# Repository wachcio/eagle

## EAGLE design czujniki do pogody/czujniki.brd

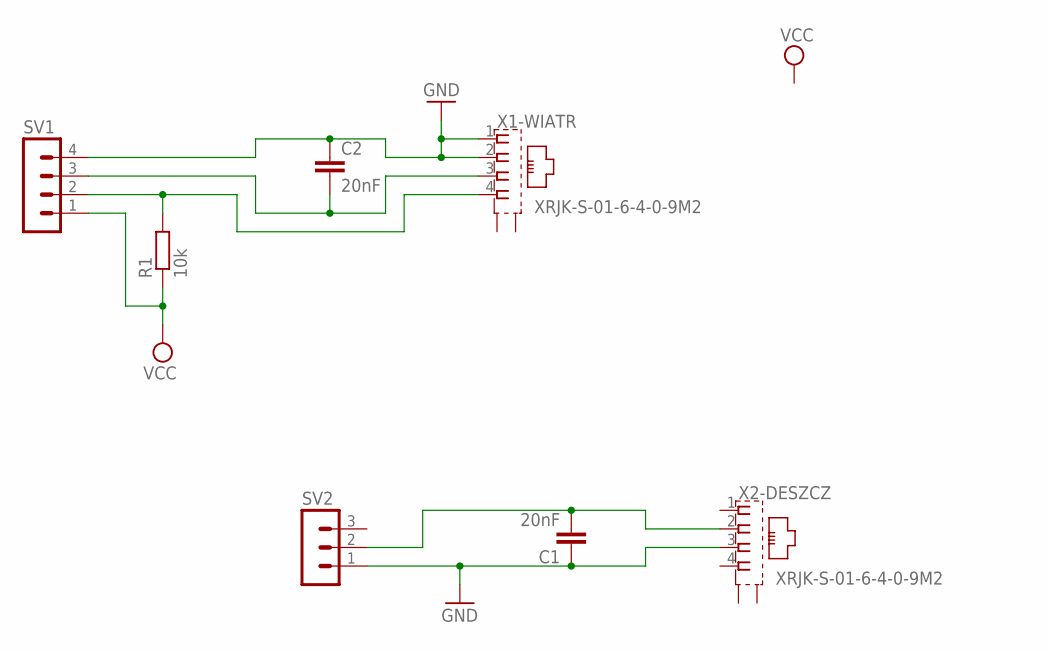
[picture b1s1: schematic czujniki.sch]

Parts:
C1, C2: 20nF; C2.5-2
R1: 10k; M1206
SV1: MA04-1
SV2: MA03-1
X1-WIATR, X2-DESZCZ: XRJK-S-01-6-4-0-9M2

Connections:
GND: C1.1, C2.1, SV1.4, SV2.1, X1-WIATR.1, X1-WIATR.2, X2-DESZCZ.3
unnamed: C1.2, SV2.2, X2-DESZCZ.2
unnamed: C2.2, SV1.3, X1-WIATR.3
unnamed: R1.2, SV1.2, X1-WIATR.4
VCC: R1.1, SV1.1

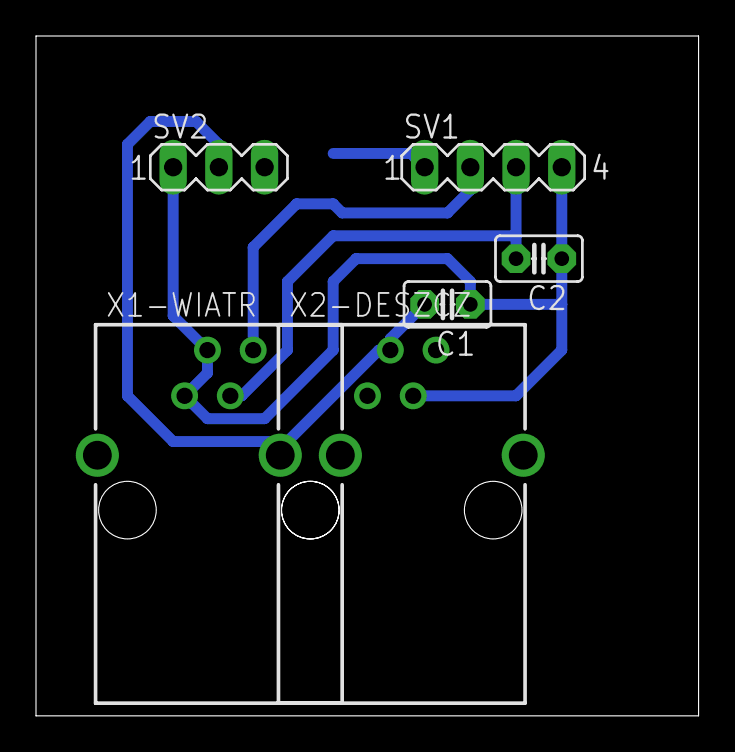
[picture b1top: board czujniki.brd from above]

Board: 2 copper layers, 36.8 x 37.8 mm, 7 parts (1 on the bottom side), 5 nets.

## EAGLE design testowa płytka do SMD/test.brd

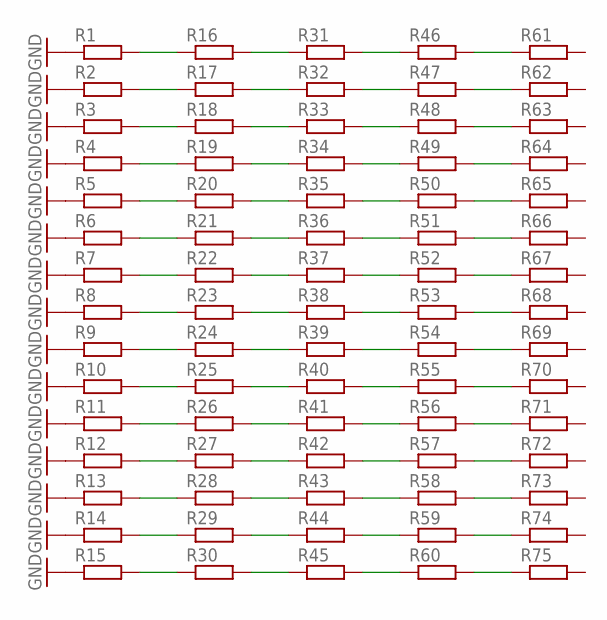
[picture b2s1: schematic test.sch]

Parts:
R1, R2, R3, R4, R5, R6, R7, R8, R9, R10, R11, R12, R13, R14, R15, R16, R17, R18, R19, R20, R21, R22, R23, R24, R25, R26, R27, R28, R29, R30, R31, R32, R33, R34, R35, R36, R37, R38, R39, R40, R41, R42, R43, R44, R45, R46, R47, R48, R49, R50, R51, R52, R53, R54, R55, R56, R57, R58, R59, R60, R61, R62, R63, R64, R65, R66, R67, R68, R69, R70, R71, R72, R73, R74, R75: R-EU_R1206; R1206

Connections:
GND: R1.1, R2.1, R3.1, R4.1, R5.1, R6.1, R7.1, R8.1, R9.1, R10.1, R11.1, R12.1, R13.1, R14.1, R15.1
unnamed: R46.2, R61.1
unnamed: R1.2, R16.1
unnamed: R2.2, R17.1
unnamed: R3.2, R18.1
unnamed: R4.2, R19.1
unnamed: R5.2, R20.1
unnamed: R6.2, R21.1
unnamed: R7.2, R22.1
unnamed: R8.2, R23.1
unnamed: R9.2, R24.1
unnamed: R10.2, R25.1
unnamed: R11.2, R26.1
unnamed: R12.2, R27.1
unnamed: R13.2, R28.1
unnamed: R14.2, R29.1
unnamed: R15.2, R30.1
unnamed: R16.2, R31.1
unnamed: R17.2, R32.1
unnamed: R18.2, R33.1
unnamed: R19.2, R34.1
unnamed: R20.2, R35.1
unnamed: R21.2, R36.1
unnamed: R22.2, R37.1
unnamed: R23.2, R38.1
unnamed: R24.2, R39.1
unnamed: R25.2, R40.1
unnamed: R26.2, R41.1
unnamed: R27.2, R42.1
unnamed: R28.2, R43.1
unnamed: R29.2, R44.1
unnamed: R30.2, R45.1
unnamed: R31.2, R46.1
unnamed: R32.2, R47.1
unnamed: R33.2, R48.1
unnamed: R34.2, R49.1
unnamed: R35.2, R50.1
unnamed: R36.2, R51.1
unnamed: R37.2, R52.1
unnamed: R38.2, R53.1
unnamed: R39.2, R54.1
unnamed: R40.2, R55.1
unnamed: R41.2, R56.1
unnamed: R42.2, R57.1
unnamed: R43.2, R58.1
unnamed: R44.2, R59.1
unnamed: R45.2, R60.1
unnamed: R47.2, R62.1
unnamed: R48.2, R63.1
unnamed: R49.2, R64.1
unnamed: R50.2, R65.1
unnamed: R51.2, R66.1
unnamed: R52.2, R67.1
unnamed: R53.2, R68.1
unnamed: R54.2, R69.1
unnamed: R55.2, R70.1
unnamed: R56.2, R71.1
unnamed: R57.2, R72.1
unnamed: R58.2, R73.1
unnamed: R59.2, R74.1
unnamed: R60.2, R75.1

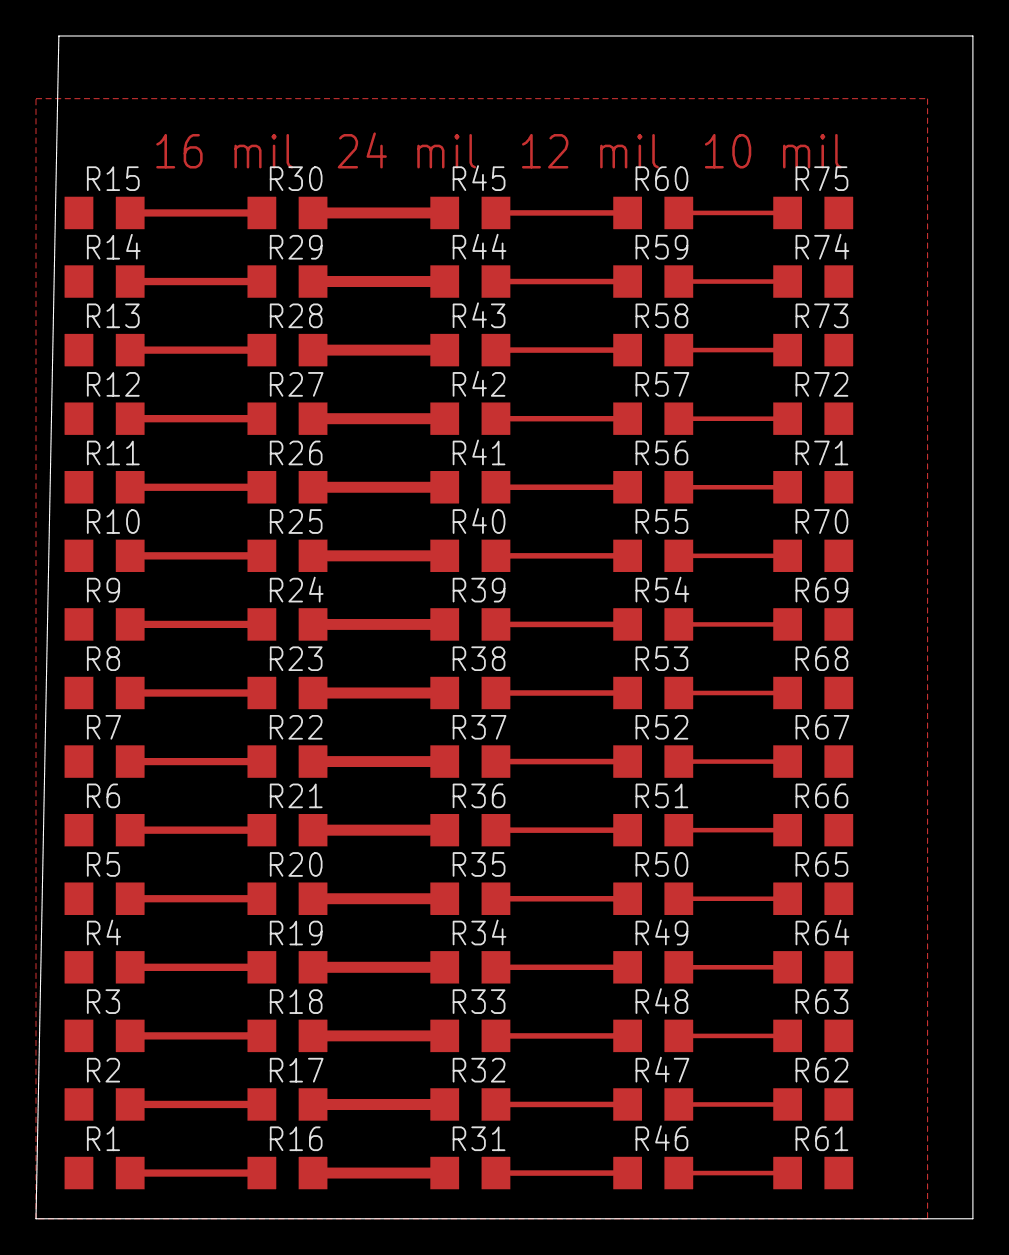
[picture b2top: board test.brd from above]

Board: 2 copper layers, 52.0 x 65.7 mm, 75 parts (0 on the bottom side), 61 nets.

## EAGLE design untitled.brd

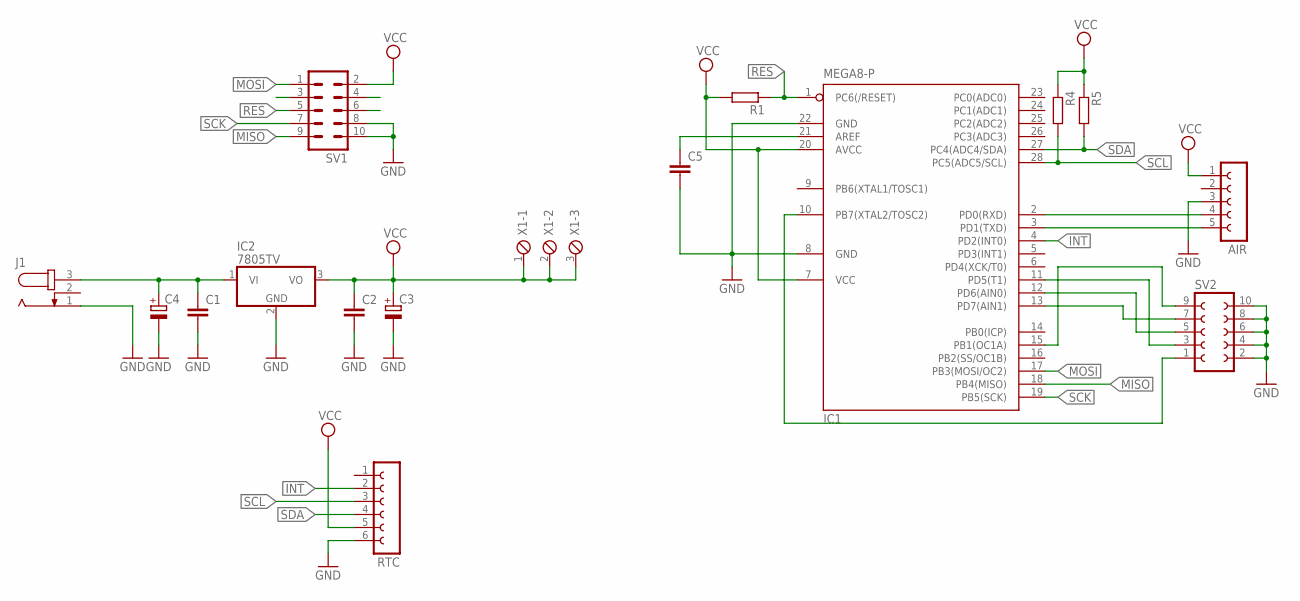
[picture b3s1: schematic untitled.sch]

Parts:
AIR: FE05-1
C1, C2, C5: C-EU025-025X050; C025-025X050
C3: CPOL-EUE2.5-5; E2,5-5
C4: CPOL-EUE3.5-8; E3,5-8
IC1: MEGA8-P; DIL28-3
IC2: 7805TV; TO220V
J1: JACK-PLUG1; SPC4078
R1, R4, R5: R-EU_0207/7; 0207/7
RTC: FE06-1; FE06
SV1: ML10
SV2: FE05-2
X1: MPT3; 3POL254

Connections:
GND: AIR.3, C1.2, C2.2, C3.-, C4.-, C5.2, IC1.8 (GND), IC1.22 (GND), IC2.2 (GND), J1.1, RTC.6, SV1.8, SV1.10, SV2.2, SV2.4, SV2.6, SV2.8, SV2.10
INT: IC1.4 (PD2(INT0)), RTC.2
MISO: IC1.18 (PB4(MISO)), SV1.9
MOSI: IC1.17 (PB3(MOSI/OC2)), SV1.1
unnamed: C1.1, C4.+, IC2.1 (VI), J1.3
unnamed: AIR.4, IC1.2 (PD0(RXD))
unnamed: AIR.5, IC1.3 (PD1(TXD))
unnamed: IC1.10 (PB7(XTAL2/TOSC2)), SV2.1
unnamed: IC1.15 (PB1(OC1A)), SV2.9
unnamed: IC1.13 (PD7(AIN1)), SV2.7
unnamed: IC1.12 (PD6(AIN0)), SV2.5
unnamed: IC1.11 (PD5(T1)), SV2.3
unnamed: C5.1, IC1.21 (AREF)
RES: IC1.1 (PC6(/RESET)), R1.1, SV1.5
SCK: IC1.19 (PB5(SCK)), SV1.7
SCL: IC1.28 (PC5(ADC5/SCL)), R4.2, RTC.3
SDA: IC1.27 (PC4(ADC4/SDA)), R5.2, RTC.4
VCC: AIR.1, C2.1, C3.+, IC1.7 (VCC), IC1.20 (AVCC), IC2.3 (VO), R1.2, R4.1, R5.1, RTC.5, SV1.2, X1.1, X1.2, X1.3

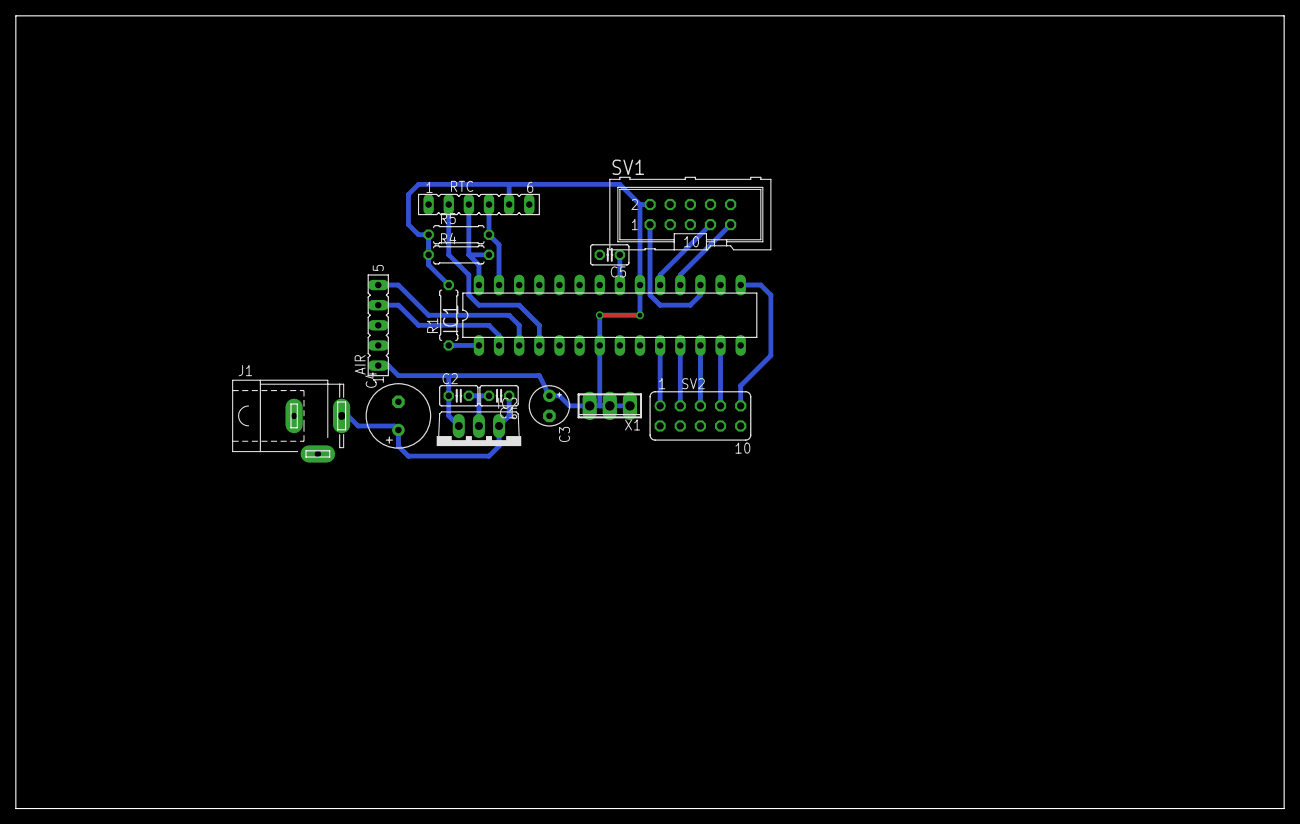
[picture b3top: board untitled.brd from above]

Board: 2 copper layers, 160.0 x 100.0 mm, 16 parts (0 on the bottom side), 18 nets.

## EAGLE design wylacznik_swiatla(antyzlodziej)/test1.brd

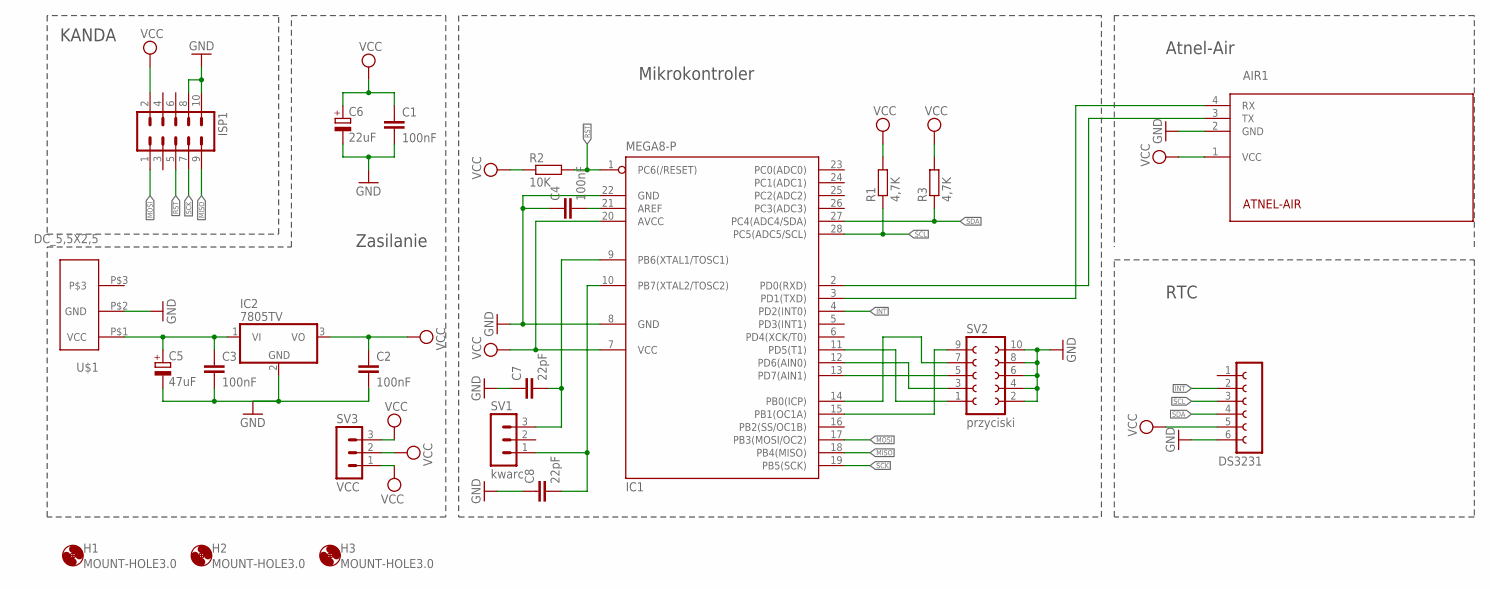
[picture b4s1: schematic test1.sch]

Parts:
AIR1: ATNEL-AIR
C1, C2, C3, C4: 100nF; C025-024X044
C5: 47uF; B45181A
C6: 22uF; B45181A
C7, C8: 22pF; C025-024X044
DS3231: FE06-1; FE06
H1, H2, H3: MOUNT-HOLE3.0; 3,0
IC1: MEGA8-P; DIL28-3
IC2: 7805TV; TO220V
ISP1: ML10
R1, R3: 4,7K; 0204/7
R2: 10K; 0204/7
SV1: kwarc; MA03-1
SV2: przyciski; FE05-2
SV3: VCC; MA03-1
U$1: DC_5,5X2,5

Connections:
GND: AIR1.2 (GND), C1.2, C2.2, C3.2, C4.1, C5.-, C6.-, C7.1, C8.1, DS3231.6, IC1.8 (GND), IC1.22 (GND), IC2.2 (GND), ISP1.8, ISP1.10, SV2.2, SV2.4, SV2.6, SV2.8, SV2.10, U$1.P$2 (GND)
INT: DS3231.2, IC1.4 (PD2(INT0))
MISO: IC1.18 (PB4(MISO)), ISP1.9
MOSI: IC1.17 (PB3(MOSI/OC2)), ISP1.1
unnamed: AIR1.3 (TX), IC1.2 (PD0(RXD))
unnamed: AIR1.4 (RX), IC1.3 (PD1(TXD))
unnamed: IC1.13 (PD7(AIN1)), SV2.5
unnamed: IC1.14 (PB0(ICP)), SV2.7
unnamed: IC1.12 (PD6(AIN0)), SV2.3
unnamed: C3.1, C5.+, IC2.1 (VI), U$1.P$1 (VCC)
unnamed: IC1.15 (PB1(OC1A)), SV2.9
unnamed: IC1.11 (PD5(T1)), SV2.1
unnamed: C4.2, IC1.21 (AREF)
unnamed: C7.2, IC1.9 (PB6(XTAL1/TOSC1)), SV1.3
unnamed: C8.2, IC1.10 (PB7(XTAL2/TOSC2)), SV1.1
RST: IC1.1 (PC6(/RESET)), ISP1.5, R2.2
SCK: IC1.19 (PB5(SCK)), ISP1.7
SCL: DS3231.3, IC1.28 (PC5(ADC5/SCL)), R1.1
SDA: DS3231.4, IC1.27 (PC4(ADC4/SDA)), R3.1
VCC: AIR1.1 (VCC), C1.1, C2.1, C6.+, DS3231.5, IC1.7 (VCC), IC1.20 (AVCC), IC2.3 (VO), ISP1.2, R1.2, R2.1, R3.2, SV3.1, SV3.2, SV3.3

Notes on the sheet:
Atnel-Air
KANDA
RTC
Zasilanie
Mikrokontroler

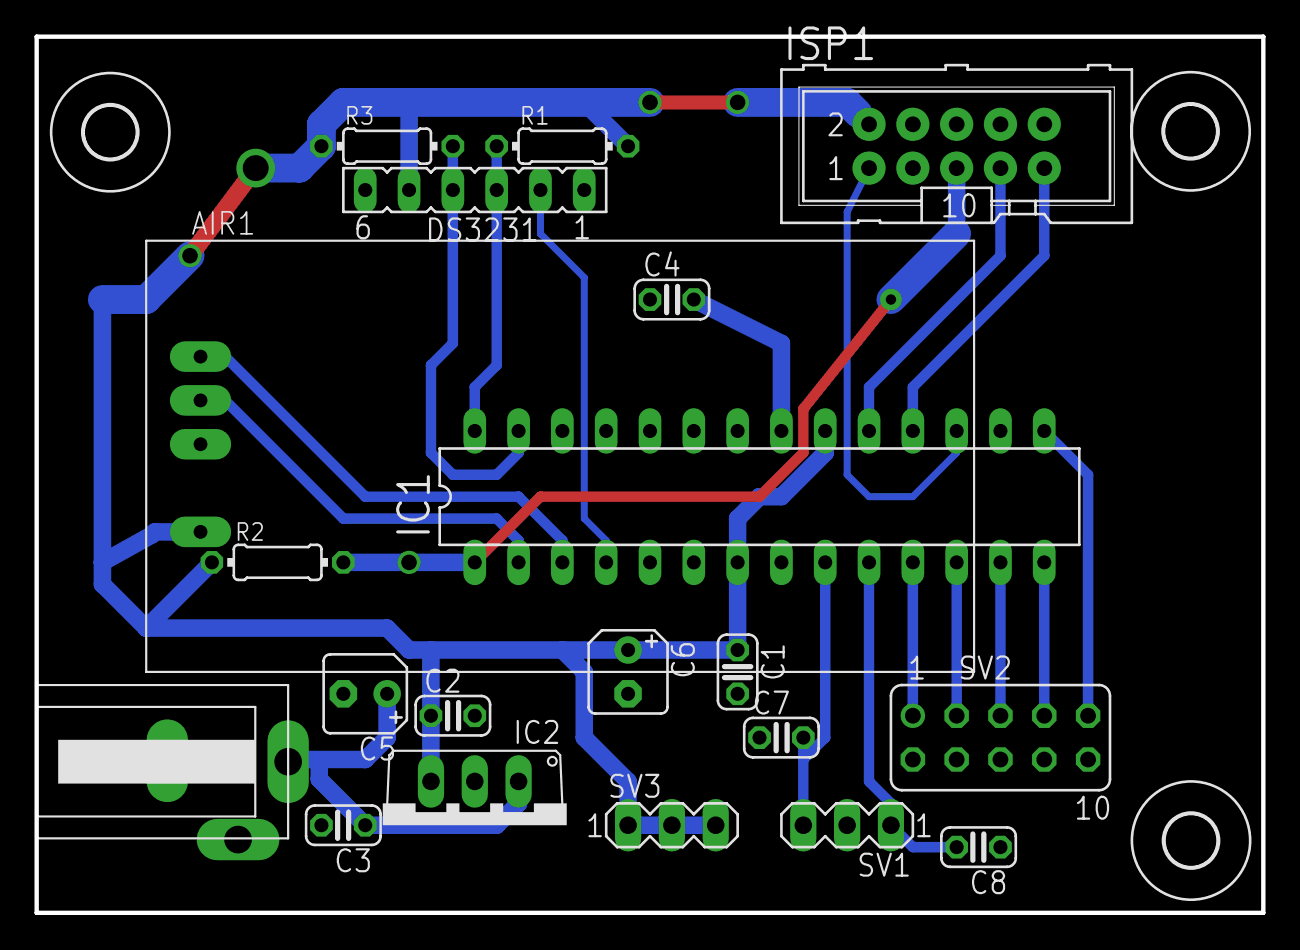
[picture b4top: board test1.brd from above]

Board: 2 copper layers, 71.1 x 50.8 mm, 23 parts (0 on the bottom side), 20 nets.

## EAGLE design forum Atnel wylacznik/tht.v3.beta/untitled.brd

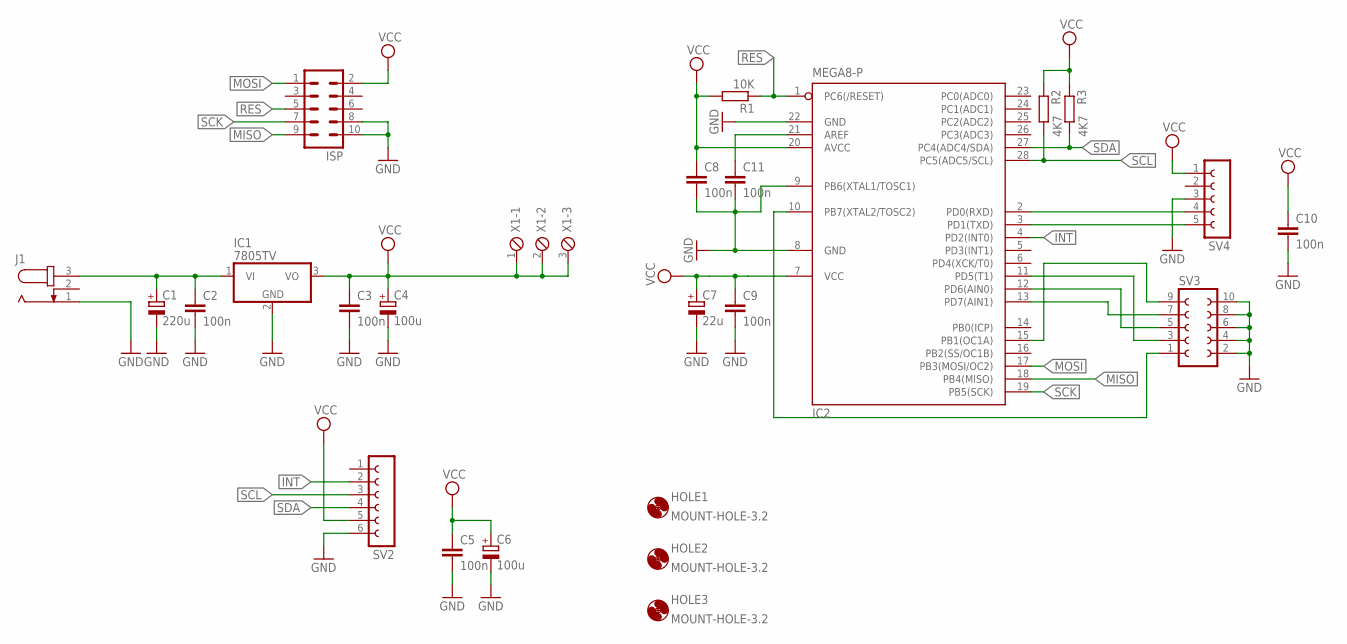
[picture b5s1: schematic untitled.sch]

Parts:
C1: 220u; E3,5-8
C2, C3, C5, C8, C10, C11: 100n; C025-025X050
C4, C6: 100u; E2,5-5
C7: 22u; E2,5-5
C9: 100n; C025-030X050
HOLE1, HOLE2, HOLE3: MOUNT-HOLE-3.2; 3,2
IC1: 7805TV; TO220V
IC2: MEGA8-P; DIL28-3
ISP: ML10
J1: JACK-PLUG1; SPC4078
R1: 10K; 0204/7
R2, R3: 4K7; 0204/7
SV2: FE06-1; FE06
SV3: FE05-2
SV4: FE05-1
X1: MPT3; 3POL254

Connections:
GND: C1.-, C2.2, C3.2, C4.-, C5.2, C6.-, C7.-, C8.2, C9.2, C10.2, C11.2, IC1.2 (GND), IC2.8 (GND), IC2.9 (PB6(XTAL1/TOSC1)), IC2.22 (GND), ISP.8, ISP.10, J1.1, SV2.6, SV3.2, SV3.4, SV3.6, SV3.8, SV3.10, SV4.3
INT: IC2.4 (PD2(INT0)), SV2.2
MISO: IC2.18 (PB4(MISO)), ISP.9
MOSI: IC2.17 (PB3(MOSI/OC2)), ISP.1
unnamed: C1.+, C2.1, IC1.1 (VI), J1.3
unnamed: C11.1, IC2.21 (AREF)
unnamed: IC2.2 (PD0(RXD)), SV4.4
unnamed: IC2.3 (PD1(TXD)), SV4.5
unnamed: IC2.10 (PB7(XTAL2/TOSC2)), SV3.1
unnamed: IC2.15 (PB1(OC1A)), SV3.9
unnamed: IC2.13 (PD7(AIN1)), SV3.7
unnamed: IC2.12 (PD6(AIN0)), SV3.5
unnamed: IC2.11 (PD5(T1)), SV3.3
RES: IC2.1 (PC6(/RESET)), ISP.5, R1.1
SCK: IC2.19 (PB5(SCK)), ISP.7
SCL: IC2.28 (PC5(ADC5/SCL)), R2.2, SV2.3
SDA: IC2.27 (PC4(ADC4/SDA)), R3.2, SV2.4
VCC: C3.1, C4.+, C5.1, C6.+, C7.+, C8.1, C9.1, C10.1, IC1.3 (VO), IC2.7 (VCC), IC2.20 (AVCC), ISP.2, R1.2, R2.1, R3.1, SV2.5, SV4.1, X1.1, X1.2, X1.3

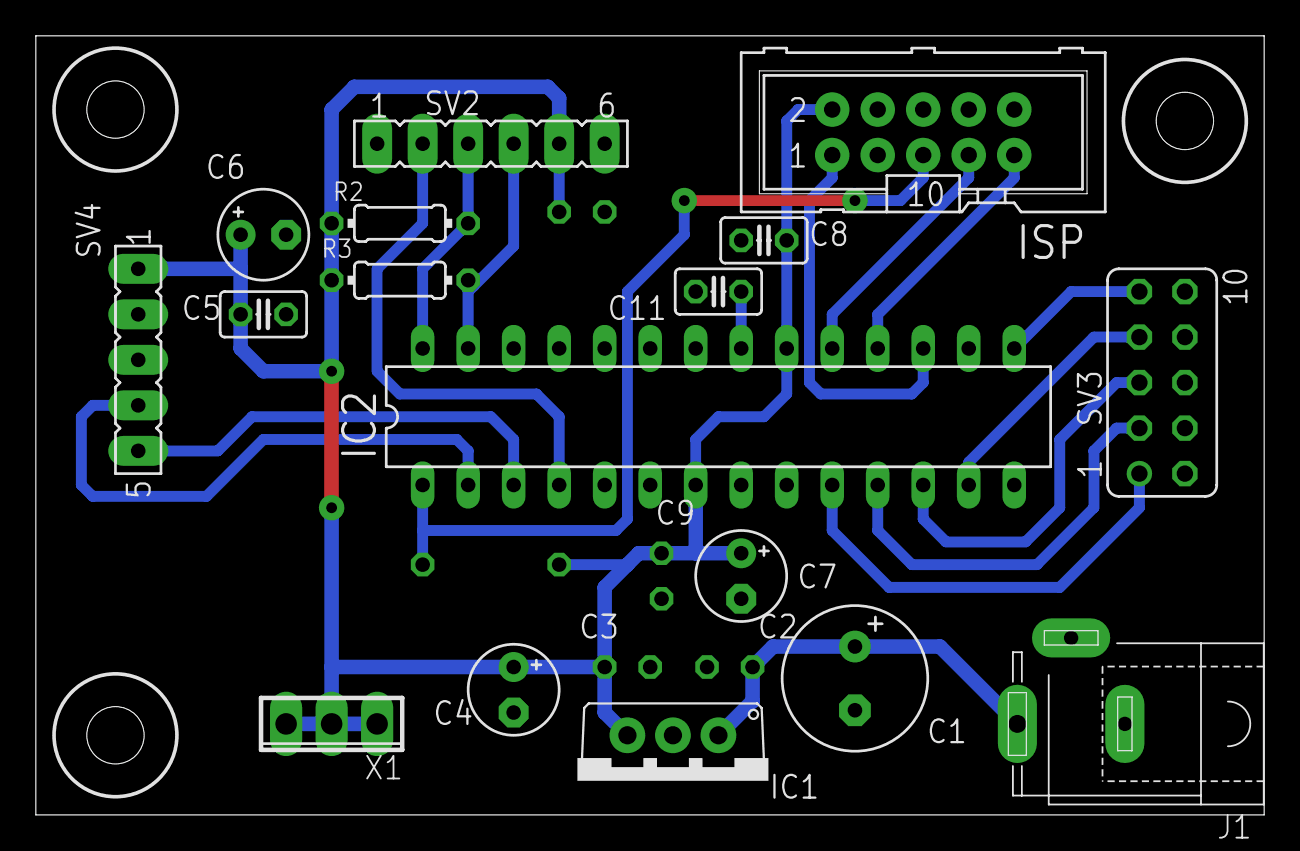
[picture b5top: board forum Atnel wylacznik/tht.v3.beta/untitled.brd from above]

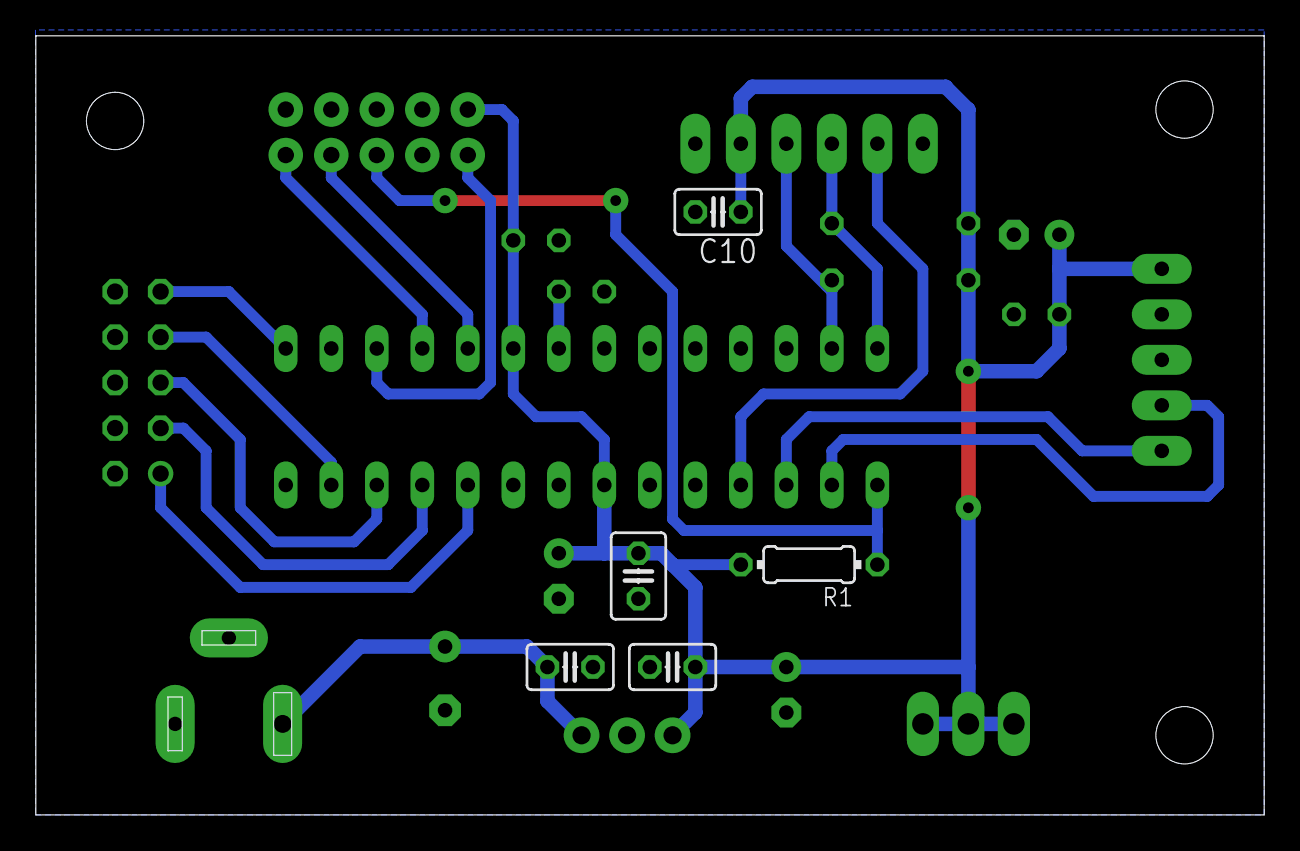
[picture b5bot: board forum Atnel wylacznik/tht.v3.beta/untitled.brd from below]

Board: 2 copper layers, 68.6 x 43.5 mm, 25 parts (5 on the bottom side), 18 nets.

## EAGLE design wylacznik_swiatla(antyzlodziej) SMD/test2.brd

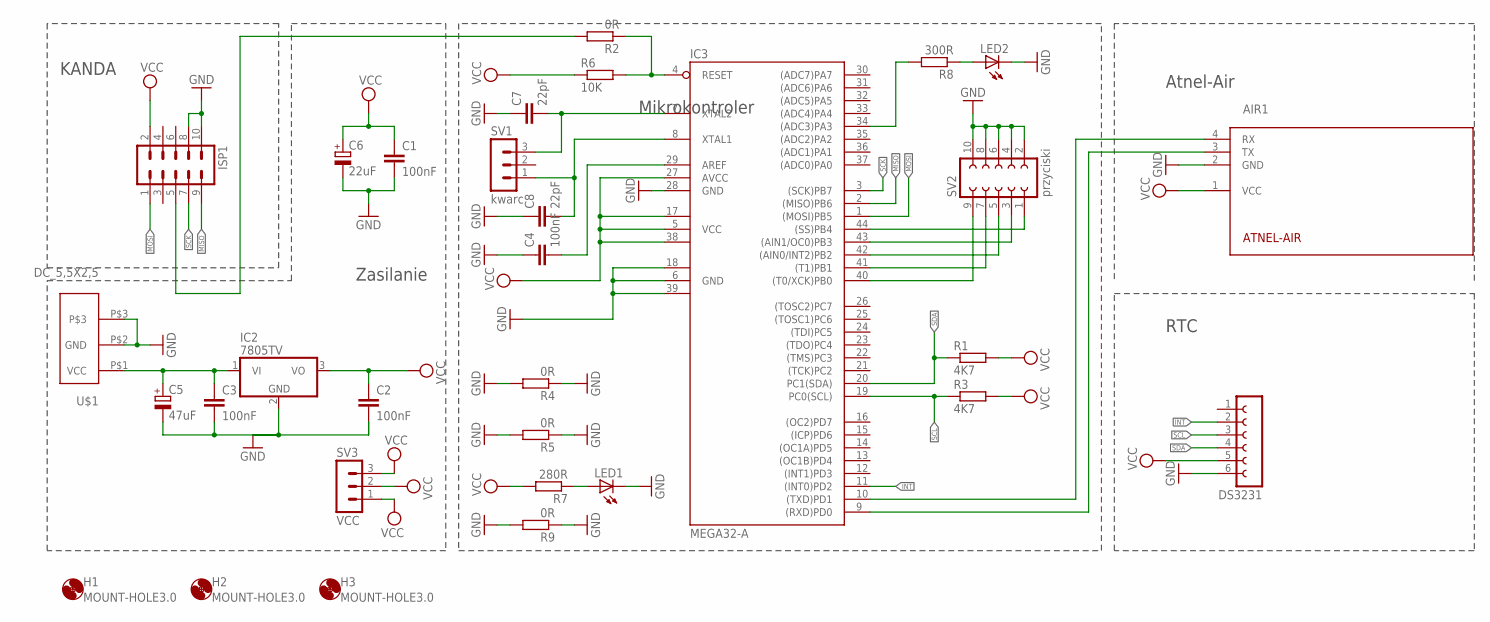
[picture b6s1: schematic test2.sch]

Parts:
AIR1: ATNEL-AIR
C1, C2, C3, C4: 100nF; C025-024X044
C5: 47uF; B45181A
C6: 22uF; B45181A
C7, C8: 22pF; C025-024X044
DS3231: FE06-1; FE06
H1, H2, H3: MOUNT-HOLE3.0; 3,0
IC2: 7805TV; TO220V
IC3: MEGA32-A; TQFP44
ISP1: ML10
LED1, LED2: LED5MM
R1, R3: 4K7; R1206W
R2, R4, R5, R9: 0R; R1206W
R6: 10K; R1206W
R7: 280R; R1206W
R8: 300R; R1206W
SV1: kwarc; MA03-1
SV2: przyciski; FE05-2
SV3: VCC; MA03-1
U$1: DC_5,5X2,5

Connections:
GND: AIR1.2 (GND), C1.2, C2.2, C3.2, C4.1, C5.-, C6.-, C7.1, C8.1, DS3231.6, IC2.2 (GND), IC3.6 (GND), IC3.18 (GND1), IC3.28 (GND), IC3.39 (GND2), ISP1.8, ISP1.10, LED1.K (C), LED2.K (C), R4.1, R4.2, R5.1, R5.2, R9.1, R9.2, SV2.2, SV2.4, SV2.6, SV2.8, SV2.10, U$1.P$2 (GND), U$1.P$3
INT: DS3231.2, IC3.11 ((INT0)PD2)
MISO: IC3.2 ((MISO)PB6), ISP1.9
MOSI: IC3.1 ((MOSI)PB5), ISP1.1
unnamed: AIR1.4 (RX), IC3.10 ((TXD)PD1)
unnamed: AIR1.3 (TX), IC3.9 ((RXD)PD0)
unnamed: C4.2, IC3.29 (AREF)
unnamed: IC3.44 ((SS)PB4), SV2.1
unnamed: IC3.43 ((AIN1/OC0)PB3), SV2.3
unnamed: C3.1, C5.+, IC2.1 (VI), U$1.P$1 (VCC)
unnamed: IC3.42 ((AIN0/INT2)PB2), SV2.5
unnamed: IC3.41 ((T1)PB1), SV2.7
unnamed: IC3.40 ((T0/XCK)PB0), SV2.9
unnamed: C7.2, IC3.7 (XTAL2), SV1.3
unnamed: C8.2, IC3.8 (XTAL1), SV1.1
unnamed: LED1.A, R7.1
unnamed: LED2.A, R8.1
unnamed: IC3.34 ((ADC3)PA3), R8.2
RST: IC3.4 (RESET), ISP1.5, R2.1, R2.2, R6.2
SCK: IC3.3 ((SCK)PB7), ISP1.7
SCL: DS3231.3, IC3.19 (PC0(SCL)), R3.1
SDA: DS3231.4, IC3.20 (PC1(SDA)), R1.1
VCC: AIR1.1 (VCC), C1.1, C2.1, C6.+, DS3231.5, IC2.3 (VO), IC3.5 (VCC), IC3.17 (VCC1), IC3.27 (AVCC), IC3.38 (VCC2), ISP1.2, R1.2, R3.2, R6.1, R7.2, SV3.1, SV3.2, SV3.3

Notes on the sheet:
Atnel-Air
KANDA
RTC
Zasilanie
Mikrokontroler

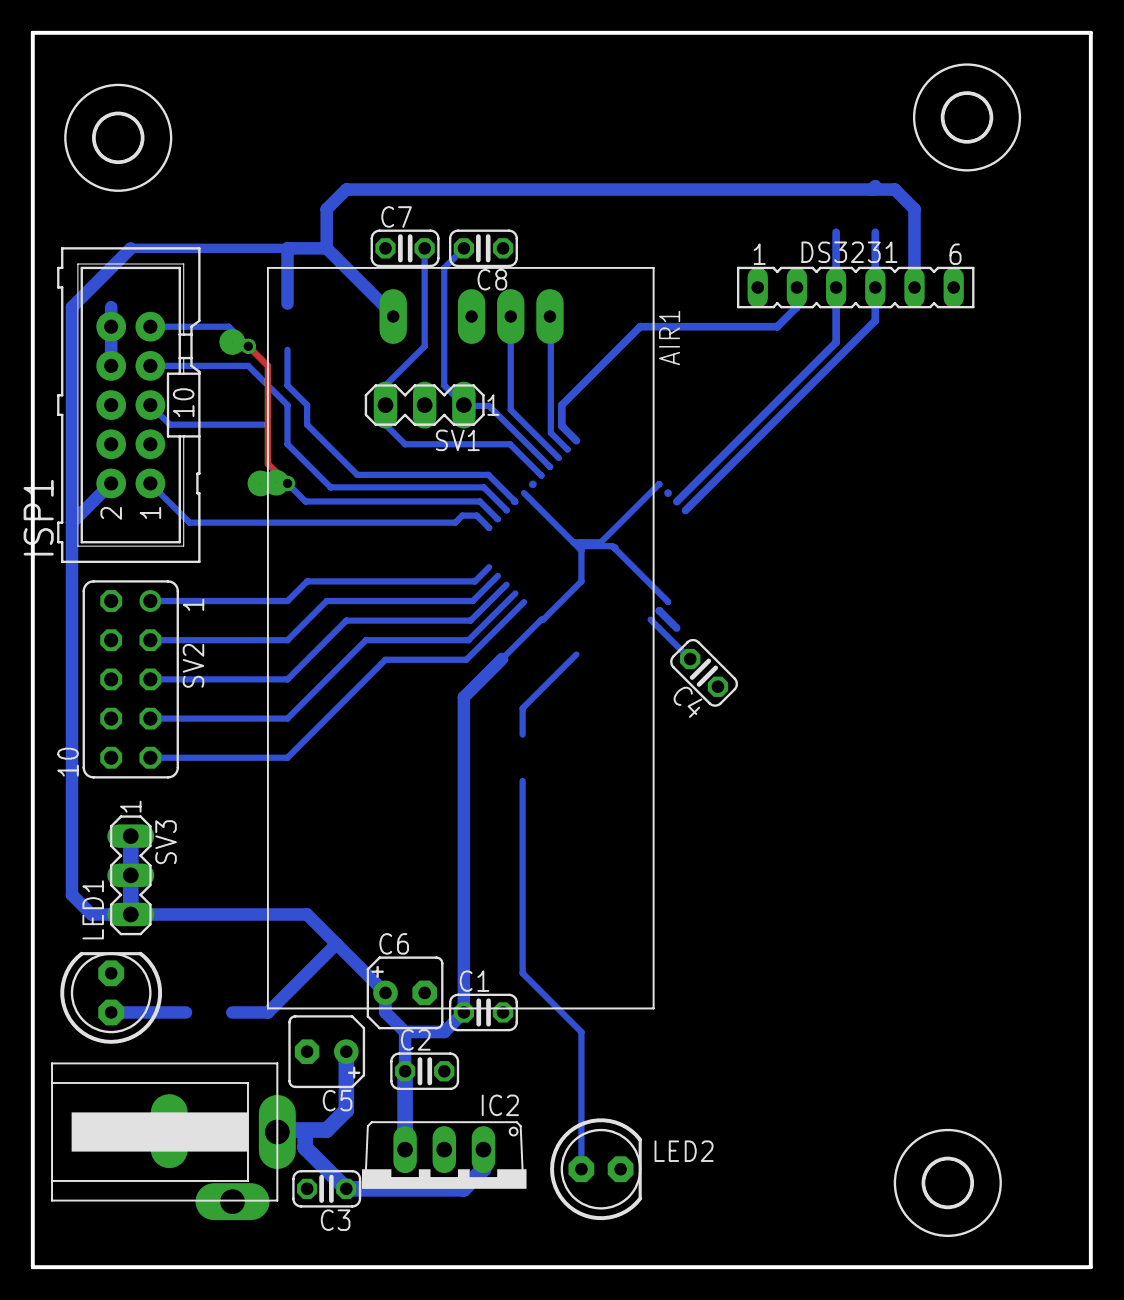
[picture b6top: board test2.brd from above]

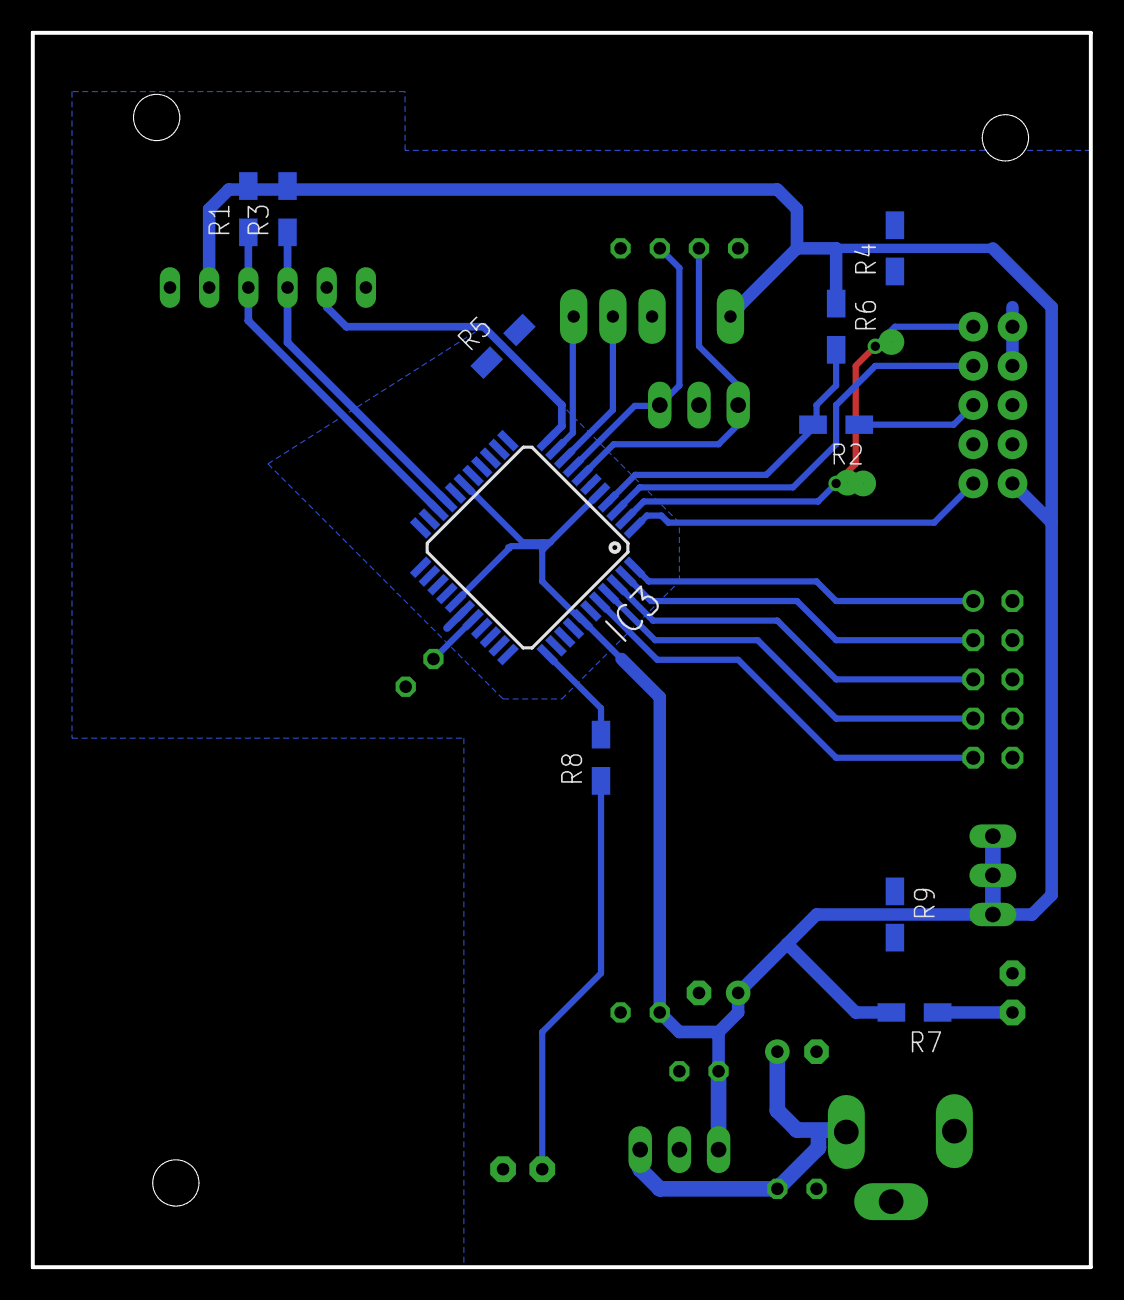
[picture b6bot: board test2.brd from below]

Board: 2 copper layers, 68.6 x 80.0 mm, 31 parts (10 on the bottom side), 23 nets.

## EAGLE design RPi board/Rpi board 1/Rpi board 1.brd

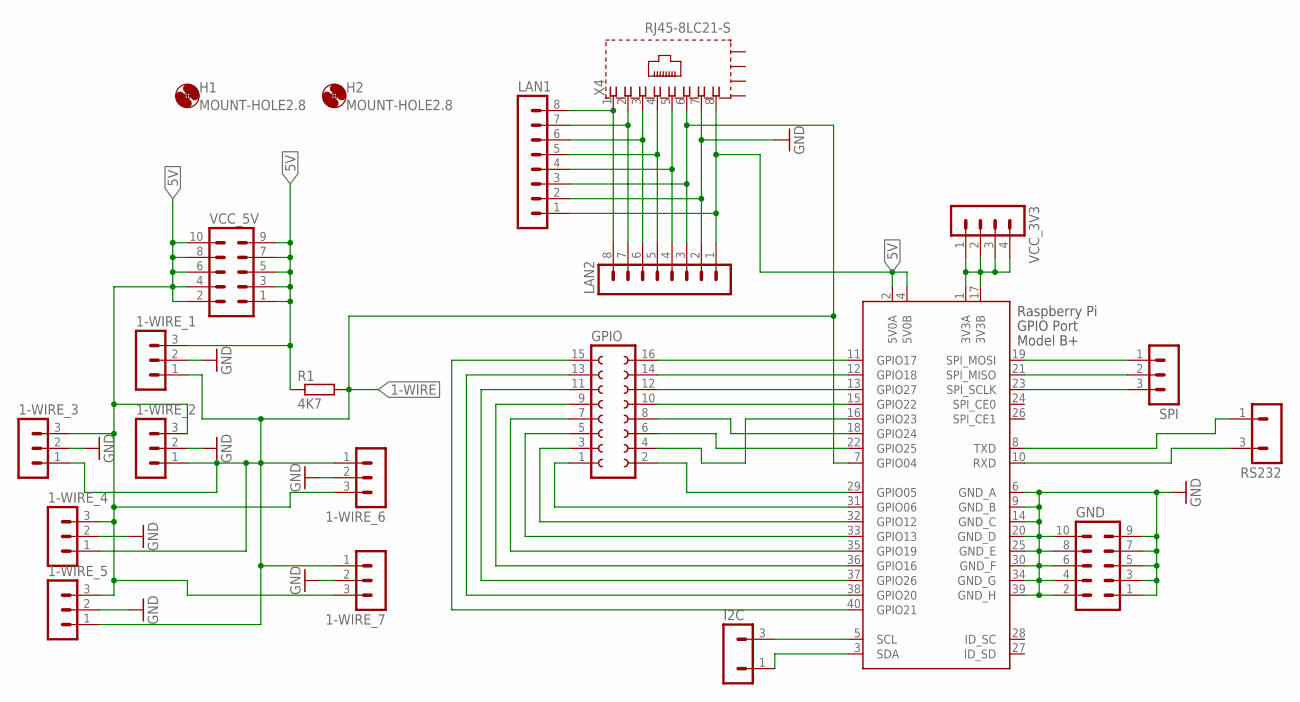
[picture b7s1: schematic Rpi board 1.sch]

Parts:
1-WIRE_1, 1-WIRE_2, 1-WIRE_3, 1-WIRE_4, 1-WIRE_5, 1-WIRE_6, 1-WIRE_7: MA03-1
GND: MA05-2
GPIO: FE08-2
H1, H2: MOUNT-HOLE2.8; 2,8
I2C: MA03-1
LAN1, LAN2: MA08-1
R1: 4K7; M0805
RS232: MA03-1
SPI: MA03-1
VCC_3V3: MA04-1
VCC_5V: MA05-2
X1: RASPI_GPIO_B+#_BOX; RASPI_GPIO_B+_BOX
X4: RJ45-8LC21-S; RJ45-SHIELD1

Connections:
1-WIRE: 1-WIRE_1.1, 1-WIRE_2.1, 1-WIRE_3.1, 1-WIRE_4.1, 1-WIRE_5.1, 1-WIRE_6.1, 1-WIRE_7.1, LAN1.3, LAN2.3, R1.2, X1.7 (GPIO04), X4.6
5V: 1-WIRE_1.3, 1-WIRE_2.3, 1-WIRE_3.3, 1-WIRE_4.3, 1-WIRE_5.3, 1-WIRE_6.3, 1-WIRE_7.3, LAN1.1, LAN2.1, R1.1, VCC_5V.1, VCC_5V.2, VCC_5V.3, VCC_5V.4, VCC_5V.5, VCC_5V.6, VCC_5V.7, VCC_5V.8, VCC_5V.9, VCC_5V.10, X1.2 (5V0A), X1.4 (5V0B), X4.8
GND: 1-WIRE_1.2, 1-WIRE_2.2, 1-WIRE_3.2, 1-WIRE_4.2, 1-WIRE_5.2, 1-WIRE_6.2, 1-WIRE_7.2, GND.1, GND.2, GND.3, GND.4, GND.5, GND.6, GND.7, GND.8, GND.9, GND.10, LAN1.2, LAN2.2, X1.6 (GND_A), X1.9 (GND_B), X1.14 (GND_C), X1.20 (GND_D), X1.25 (GND_E), X1.30 (GND_F), X1.34 (GND_G), X1.39 (GND_H), X4.7
unnamed: RS232.1, X1.8 (TXD)
unnamed: VCC_3V3.1, VCC_3V3.2, VCC_3V3.3, VCC_3V3.4, X1.1 (3V3A), X1.17 (3V3B)
unnamed: RS232.3, X1.10 (RXD)
unnamed: SPI.1, X1.19 (SPI_MOSI)
unnamed: SPI.2, X1.21 (SPI_MISO)
unnamed: SPI.3, X1.23 (SPI_SCLK)
unnamed: I2C.3, X1.5 (SCL)
unnamed: I2C.1, X1.3 (SDA)
unnamed: GPIO.16, X1.11 (GPIO17)
unnamed: GPIO.14, X1.12 (GPIO18)
unnamed: GPIO.12, X1.13 (GPIO27)
unnamed: GPIO.10, X1.15 (GPIO22)
unnamed: GPIO.8, X1.18 (GPIO24)
unnamed: GPIO.6, X1.22 (GPIO25)
unnamed: GPIO.4, X1.16 (GPIO23)
unnamed: GPIO.2, X1.29 (GPIO05)
unnamed: GPIO.1, X1.31 (GPIO06)
unnamed: GPIO.3, X1.32 (GPIO12)
unnamed: GPIO.5, X1.33 (GPIO13)
unnamed: GPIO.7, X1.35 (GPIO19)
unnamed: GPIO.9, X1.36 (GPIO16)
unnamed: GPIO.11, X1.37 (GPIO26)
unnamed: GPIO.13, X1.38 (GPIO20)
unnamed: GPIO.15, X1.40 (GPIO21)
unnamed: LAN1.4, LAN2.4, X4.5
unnamed: LAN1.5, LAN2.5, X4.4
unnamed: LAN1.6, LAN2.6, X4.3
unnamed: LAN1.7, LAN2.7, X4.2
unnamed: LAN1.8, LAN2.8, X4.1

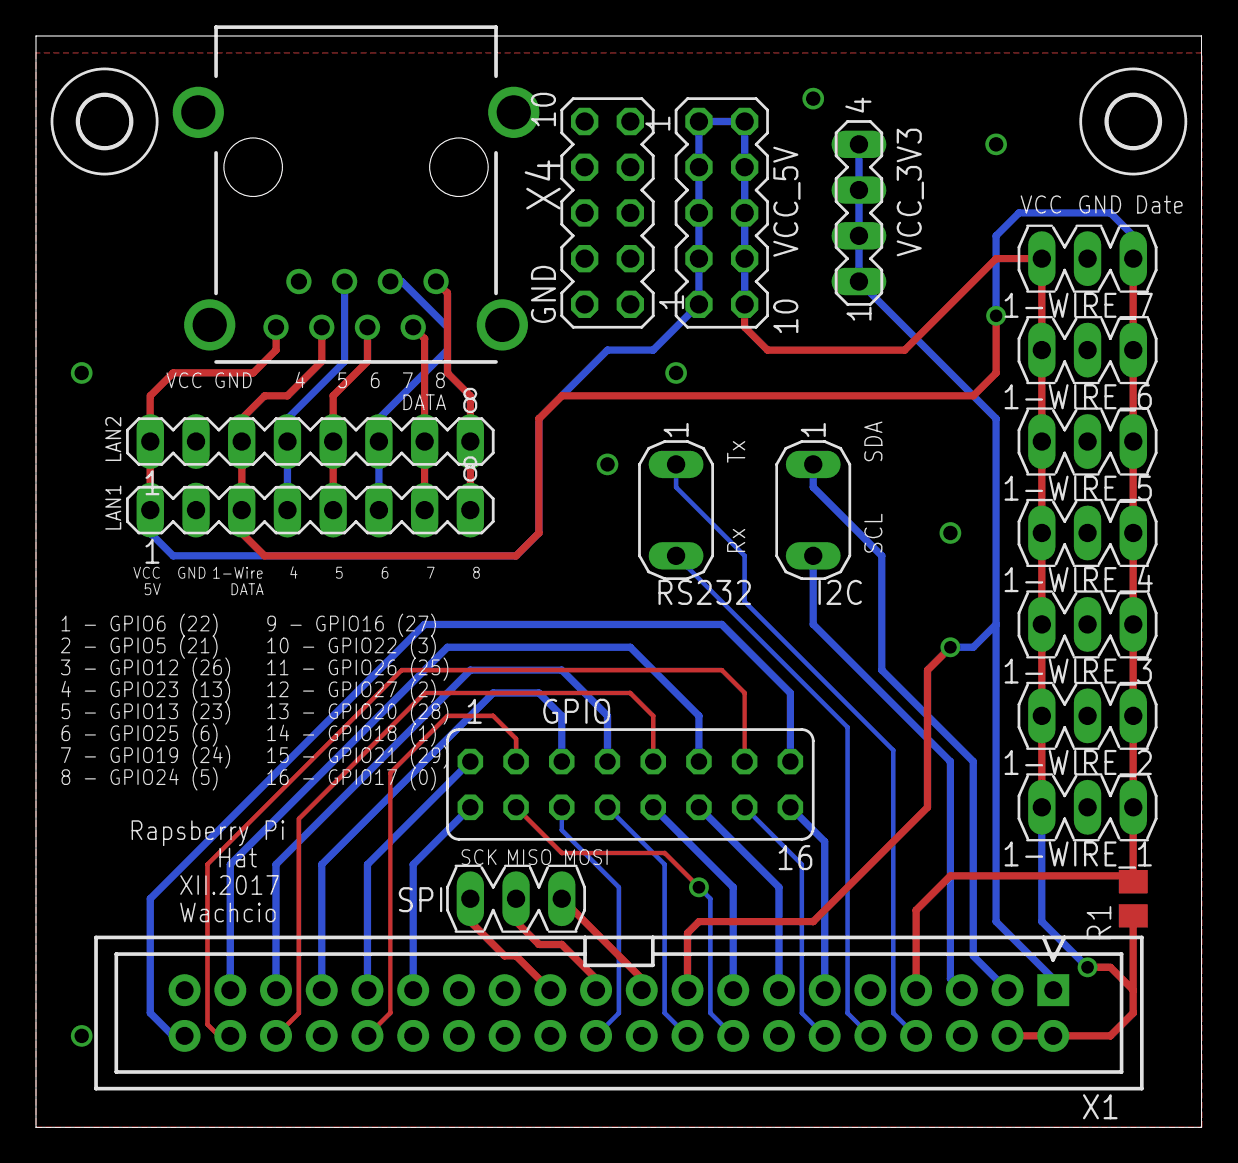
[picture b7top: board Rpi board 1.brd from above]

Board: 2 copper layers, 64.8 x 60.6 mm, 21 parts (0 on the bottom side), 32 nets.

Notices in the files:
parts and their libraries:
SparkFun-Sensors: Licensing: Creative Commons ShareAlike 4.0 International - https://creativecommons.org/licenses/by-sa/4.0
